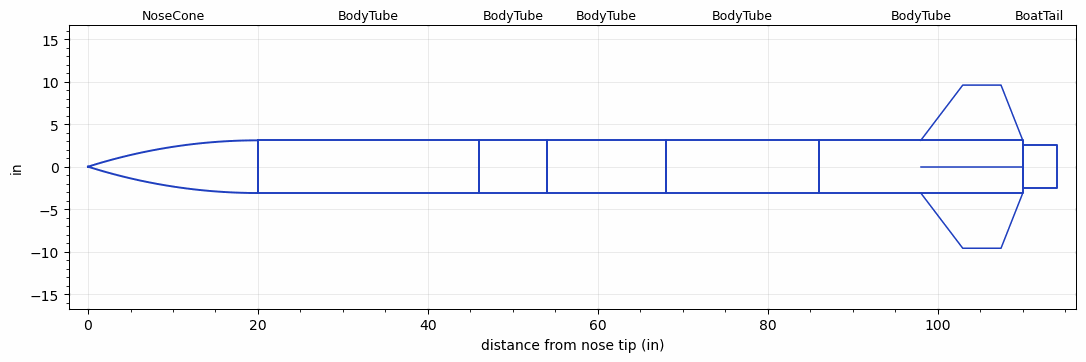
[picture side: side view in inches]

<RASAeroDocument>
 <FileVersion>2</FileVersion>
 <RocketDesign>
  <NoseCone>
   <Length>20</Length>
   <Diameter>6.2</Diameter>
   <Shape>Tangent Ogive</Shape>
   <Location>0</Location>
  </NoseCone>
  <BodyTube>
   <Length>25.9999</Length>
   <Diameter>6.2</Diameter>
   <Location>20</Location>
  </BodyTube>
  <BodyTube>
   <Length>8</Length>
   <Diameter>6.2</Diameter>
   <Location>45.9999</Location>
  </BodyTube>
  <BodyTube>
   <Length>14</Length>
   <Diameter>6.2</Diameter>
   <Location>53.9999</Location>
  </BodyTube>
  <BodyTube>
   <Length>18</Length>
   <Diameter>6.2</Diameter>
   <Location>67.9999</Location>
  </BodyTube>
  <BodyTube>
   <Length>24</Length>
   <Diameter>6.2</Diameter>
   <RailGuideDiameter>0.621</RailGuideDiameter>
   <RailGuideHeight>0.6845</RailGuideHeight>
   <Location>85.9998</Location>
   <Fin>
    <Count>4</Count>
    <Chord>12</Chord>
    <Span>6.5</Span>
    <SweepDistance>4.937</SweepDistance>
    <TipChord>4.5</TipChord>
    <Thickness>0.125</Thickness>
    <Location>12</Location>
    <AirfoilSection>Rounded</AirfoilSection>
   </Fin>
  </BodyTube>
  <BoatTail>
   <Length>4</Length>
   <Diameter>5</Diameter>
   <RearDiameter>5</RearDiameter>
   <Location>109.9998</Location>
  </BoatTail>
  <Surface>Sheet Metal</Surface>
  <CD>0</CD>
  <ModifiedBarrowman>False</ModifiedBarrowman>
  <Turbulence>False</Turbulence>
  <UseBooster1>False</UseBooster1>
  <UseBooster2>False</UseBooster2>
 </RocketDesign>
 <LaunchSite>
  <Altitude>2870.735</Altitude>
  <Pressure>28.9828</Pressure>
  <RodAngle>5</RodAngle>
  <RodLength>163.9997</RodLength>
  <Temperature>77</Temperature>
  <WindSpeed>15</WindSpeed>
 </LaunchSite>
 <Recovery>
  <Altitude1>1476.378</Altitude1>
  <Altitude2>656.168</Altitude2>
  <DeviceType1>Parachute</DeviceType1>
  <DeviceType2>Parachute</DeviceType2>
  <Event1>True</Event1>
  <Event2>True</Event2>
  <Size1>91.1998</Size1>
  <Size2>22.9</Size2>
  <EventType1>Altitude</EventType1>
  <EventType2>Apogee</EventType2>
  <CD1>2.19</CD1>
  <CD2>0</CD2>
 </Recovery>
 <SimulationList>
  <Simulation>
   <SustainerLaunchWt>65.0879</SustainerLaunchWt>
   <SustainerCG>70.2443</SustainerCG>
   <SustainerIgnitionDelay>0</SustainerIgnitionDelay>
   <Booster1SeparationDelay>0</Booster1SeparationDelay>
   <Booster1IgnitionDelay>0</Booster1IgnitionDelay>
   <IncludeBooster1>False</IncludeBooster1>
   <Booster2Delay>0</Booster2Delay>
   <IncludeBooster2>False</IncludeBooster2>
  </Simulation>
 </SimulationList>
</RASAeroDocument>
